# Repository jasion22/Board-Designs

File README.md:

# Gateway_Docking_Station
This project focuses on creating a gateway system that connects remote and host networks using a Raspberry Pi 3B+ and an RAK 833 (a LoRaWAN concentrator). This 

# Getting Started
- Make sure that you have a C1_Node_revb_v1.0.
- Raspberry Pi 3B+.
- RAK 833.

# Prerequisites
Board [Tested]

# Contributing
Instructions coming up soon.

# License
This project is licensed under the MIT License - see the LICENSE.md file for details

# Acknowledgments

# Changelog

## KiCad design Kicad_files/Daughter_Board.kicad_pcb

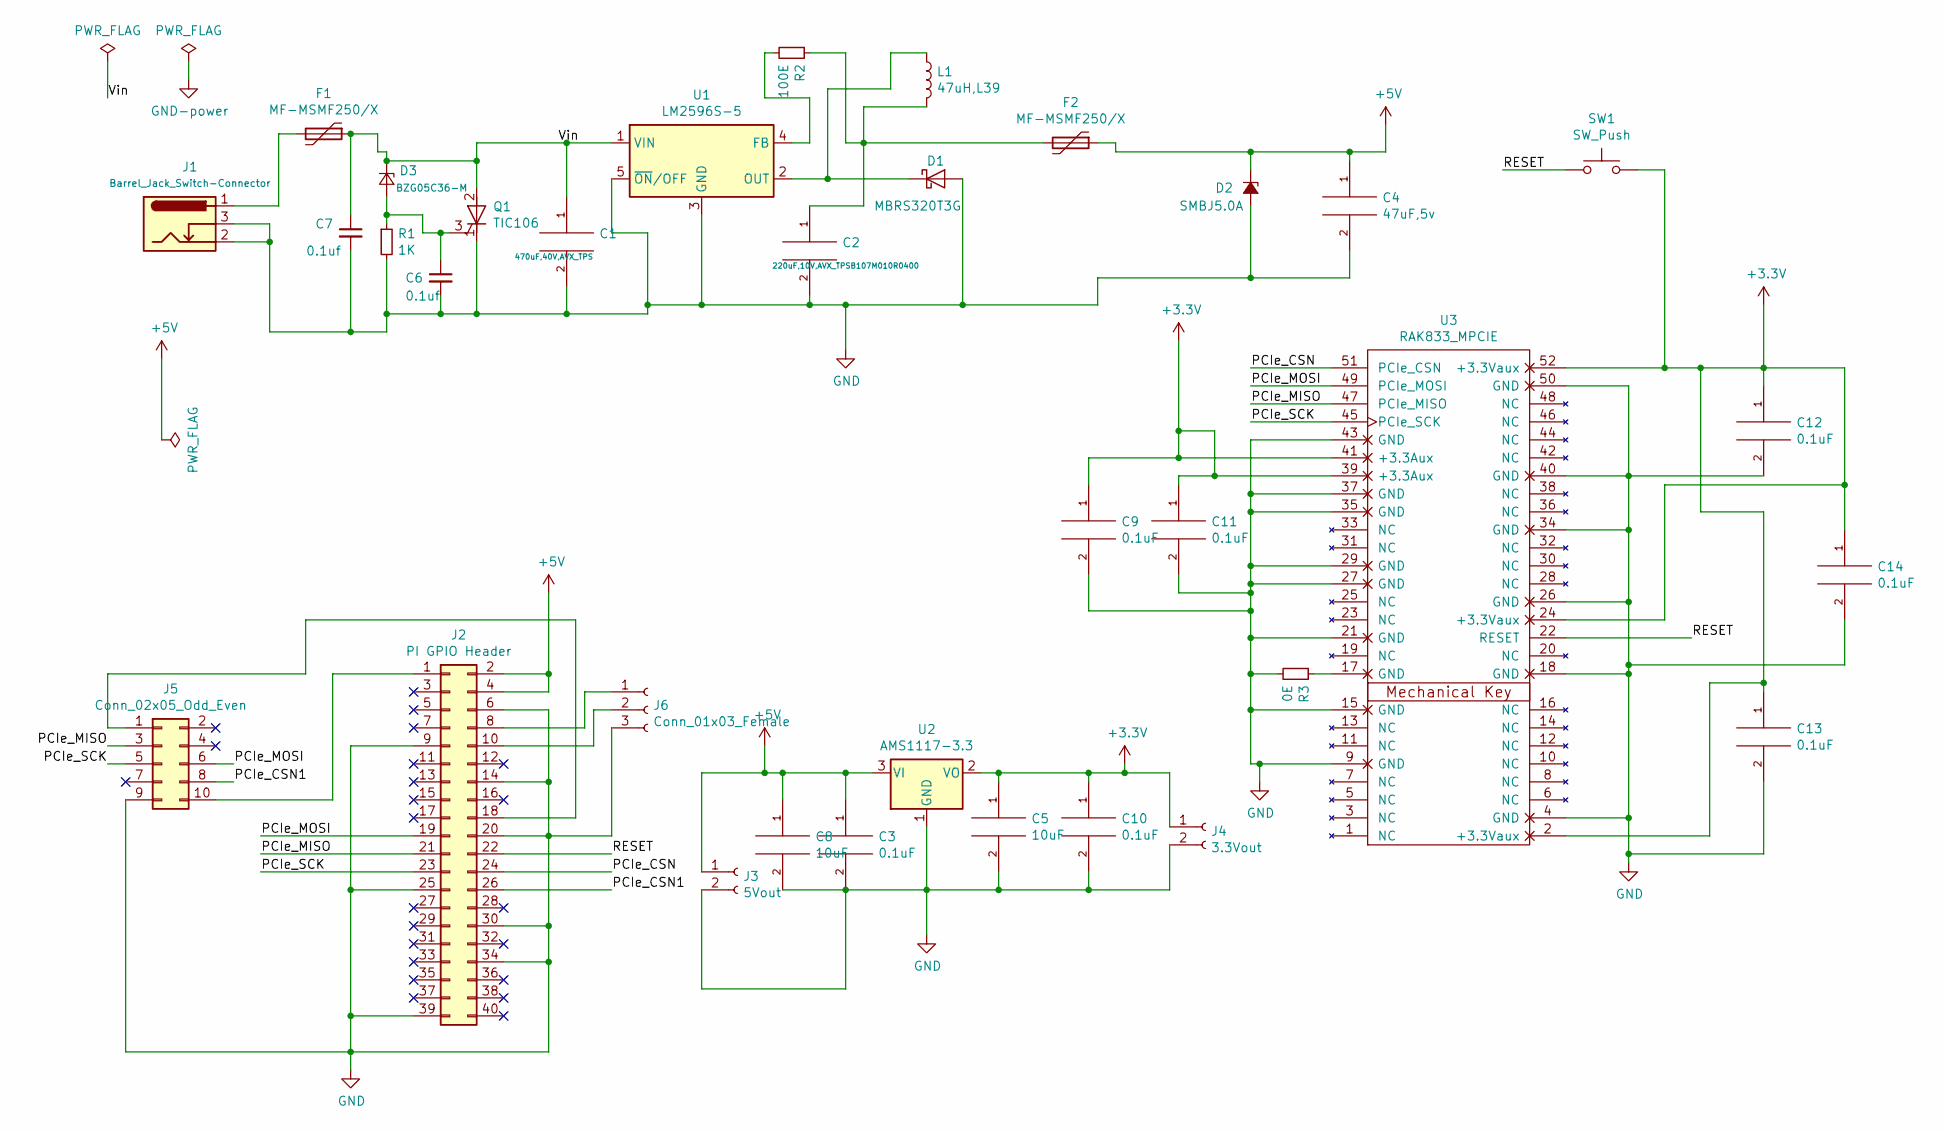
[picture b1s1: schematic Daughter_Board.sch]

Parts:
C1: 470uF,40V,AVX_TPS; CP_Elec_10x14.3
C2: 220uF,10V,AVX_TPSB107M010R0400; CP_Elec_8x10
C3, C9, C10, C11, C12, C13, C14: 0.1uF; C_0805_2012Metric
C4: 47uF,5v; C_0805_2012Metric
C5, C8: 10uF; C_0805_2012Metric
C6, C7: 0.1uf; C_1206_3216Metric
D1: MBRS320T3G; MBRS320T3G_Metric
D2: SMBJ5.0A; SMBJ5.0A_Metric
D3: BZG05C36-M; BZG05C36-M3-08_Metric
F1, F2: MF-MSMF250/X; Fuse_1812_4532Metric
J1: Barrel_Jack_Switch-Connector; BarrelJack_CUI_PJ-102AH_Horizontal
J2: PI GPIO Header; PinSocket_2x20_P2.54mm_Vertical
J3: 5Vout; JST_EH_B2B-EH-A_1x02_P2.50mm_Vertical
J4: 3.3Vout; JST_EH_B2B-EH-A_1x02_P2.50mm_Vertical
J5: Conn_02x05_Odd_Even; Samtec_HLE-105-02-xx-DV-TE_2x05_P2.54mm_Horizontal
J6: Conn_01x03_Female; JST_EH_B3B-EH-A_1x03_P2.50mm_Vertical
L1: 47uH,L39; L_12x12mm_H8mm
Q1: TIC106; TO-220-3_Vertical
R1: 1K; R_0603_1608Metric
R2: 100E; R_Axial_DIN0207_L6.3mm_D2.5mm_P7.62mm_Horizontal
R3: 0E; R_0603_1608Metric
SW1: SW_Push; SW_DIP_SPSTx01_Slide_6.7x4.1mm_W6.73mm_P2.54mm_LowProfile_J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
U1: LM2596S-5; TO-263-5_TabPin3
U2: AMS1117-3.3; SOT-223-3_TabPin2
U3: RAK833_MPCIE; mpcie-socket

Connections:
+3V3: C5.1, C9.1, C10.1, C11.1, C12.1, C13.1, C14.1, J4.1, SW1.2, U2.2 (VO), U3.2 (+3.3Vaux), U3.24 (+3.3Vaux), U3.39 (+3.3Aux), U3.41 (+3.3Aux), U3.52 (+3.3Vaux)
+5V: C3.1, C4.1, C8.1, D2.1 (K), F2.1, J2.2, J2.4, J3.1, U2.3 (VI)
/PCIe_CSN: J2.24, U3.51 (PCIe_CSN)
/PCIe_CSN1: J2.26, J5.8
/PCIe_MISO: J2.21, J5.3, U3.47 (PCIe_MISO)
/PCIe_MOSI: J2.19, J5.6, U3.49 (PCIe_MOSI)
/PCIe_SCK: J2.23, J5.5, U3.45 (PCIe_SCK)
/RESET: J2.22, SW1.1, U3.22 (RESET)
/Vin: C1.1, C7.1, D3.1 (K), F1.1, Q1.2 (A), U1.1 (VIN)
GND: C1.2, C2.2, C3.2, C4.2, C5.2, C6.2, C7.2, C8.2, C9.2, C10.2, C11.2, C12.2, C13.2, C14.2, D1.2 (A), D2.2 (A), J1.2, J1.3, J2.6, J2.9, J2.14, J2.20, J2.25, J2.30, J2.34, J2.39, J3.2, J4.2, J5.9, J6.3, Q1.1 (K), R1.2, R3.2, U1.3 (GND), U1.5 (~ON~/OFF), U2.1 (GND), U3.4 (GND), U3.9 (GND), U3.15 (GND), U3.18 (GND), U3.21 (GND), U3.26 (GND), U3.27 (GND), U3.29 (GND), U3.34 (GND), U3.35 (GND), U3.37 (GND), U3.40 (GND), U3.43 (GND), U3.50 (GND)
unnamed: C2.1, F2.2, L1.2, R2.1
unnamed: C6.1, D3.2 (A), Q1.3 (G), R1.1
unnamed: D1.1 (K), L1.1, U1.2 (OUT)
unnamed: F1.2, J1.1
unnamed: J2.1, J5.10
unnamed: J2.8, J6.1
unnamed: J2.10, J6.2
unnamed: J2.18, J5.1
unnamed: R2.2, U1.4 (FB)
unnamed: R3.1, U3.17 (GND)

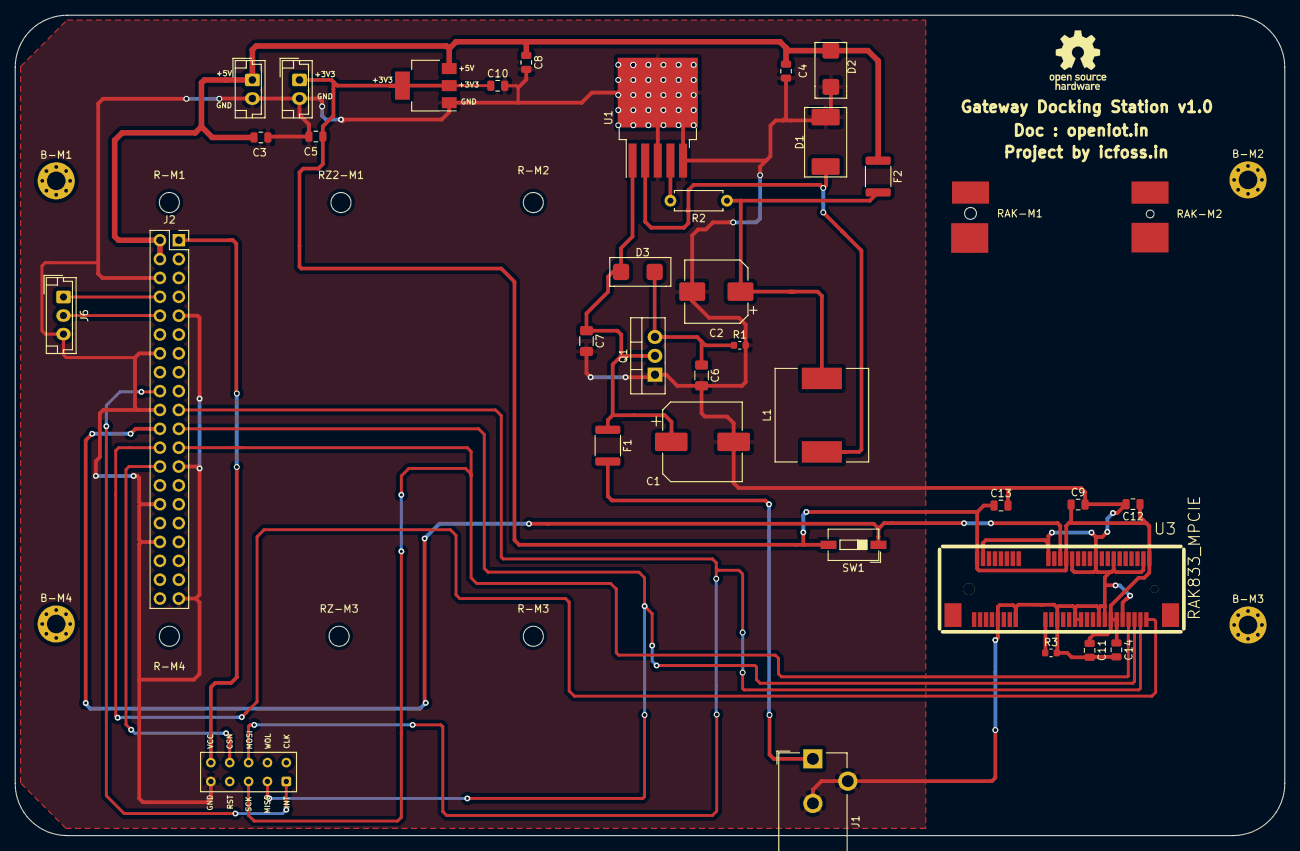
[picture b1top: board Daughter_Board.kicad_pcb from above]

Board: 2 copper layers, 171.0 x 110.5 mm, 46 parts (0 on the bottom side), 20 nets.

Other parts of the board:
B-M1, B-M2, B-M3, B-M4: MountingHole_2.5mm_Pad_Via
R-M1, R-M2, R-M3, R-M4: MountingHole_2.7mm_M2.5
RAK-M1, RAK-M2: MountingHole_2.1mm
RZ2-M1: MountingHole_2.7mm_M2.5
RZ-M3: MountingHole_2.7mm_M2.5

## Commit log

2024-12-13 updated files
